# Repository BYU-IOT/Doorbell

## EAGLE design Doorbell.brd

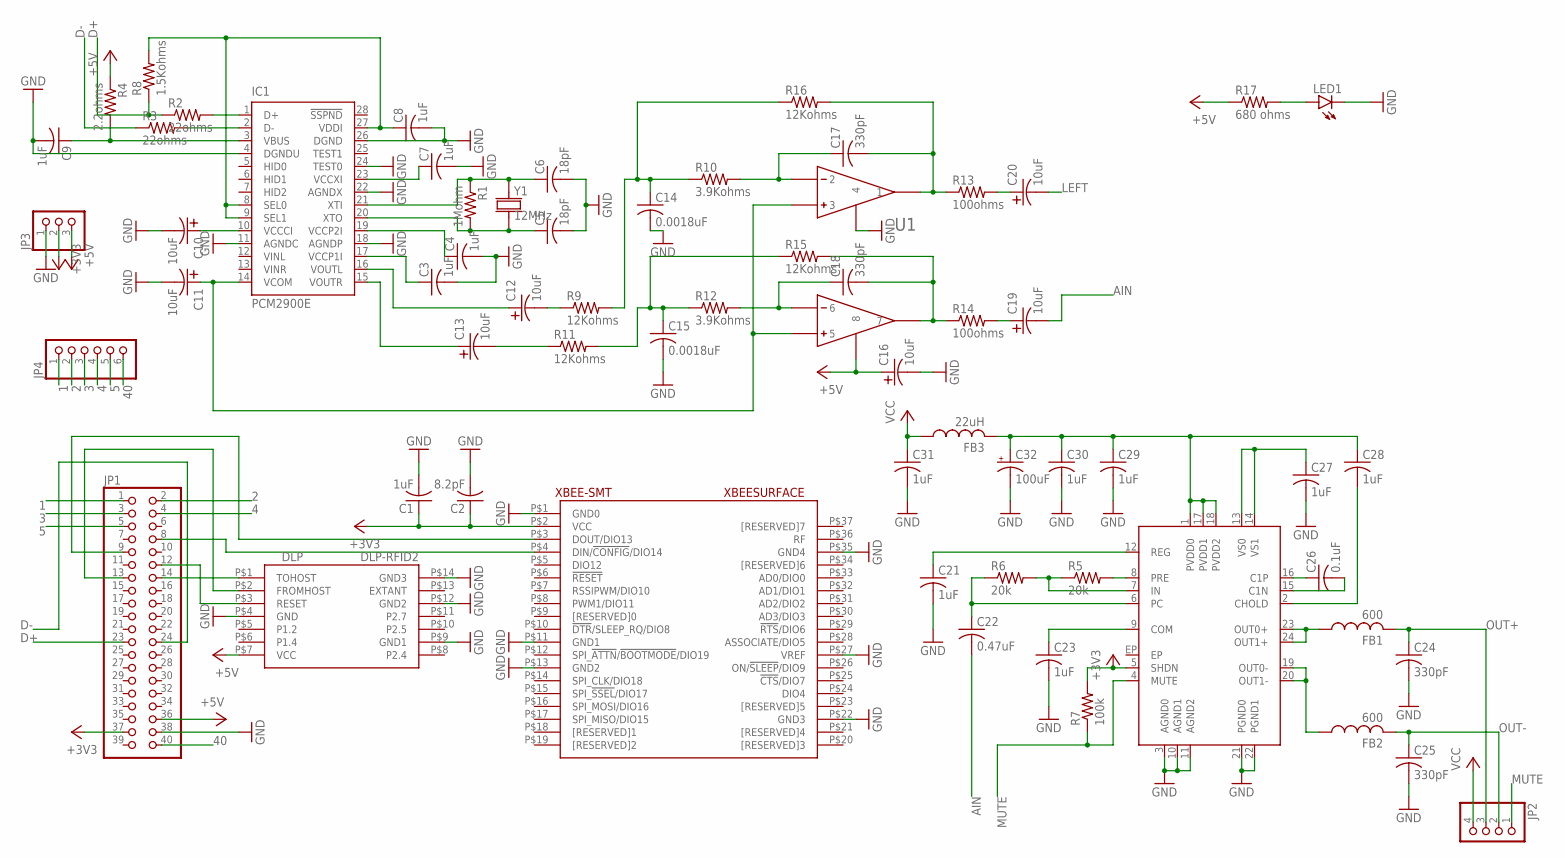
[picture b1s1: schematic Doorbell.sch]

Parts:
C1, C3, C4, C7, C8, C9, C21, C23, C27, C28, C29, C30, C31: 1uF; 0603_CAP
C2: 8.2pF; 0603_CAP
C5, C6: 18pF; 0603_CAP
C10, C11, C12, C13, C16, C19, C20: 10uF; 1411_CAP
C14, C15: 0.0018uF; 0603_CAP
C17, C18, C24, C25: 330pF; 0603_CAP
C22: 0.47uF; 0603_CAP
C26: 0.1uF; 0603_CAP
C32: 100uF; F_CAP
DLP: DLP-RFID2
FB1, FB2: 600; 0805_FB
FB3: 22uH; 0805_FB
IC1: PCM2900E; SSOP28DB
IC2: MAX9737; TQFN24
JP1: PINHD-2X20; 2X20
JP2: PINHD-1X4; 1X04
JP3: PINHD-1X3; 1X03
JP4: PINHD-1X6; 1X06
LED1: LED0603; 0603_LED
R1: 1Mohm; 0603_RESISTOR
R2, R3: 22ohms; 0603_RESISTOR
R4: 2.2ohms; 0603_RESISTOR
R5, R6: 20k; 0603_RESISTOR
R7: 100k; 0603_RESISTOR
R8: 1.5Kohms; 0603_RESISTOR
R9, R11, R15, R16: 12Kohms; 0603_RESISTOR
R10, R12: 3.9Kohms; 0603_RESISTOR
R13, R14: 100ohms; 0603_RESISTOR
R17: 680 ohms; 0603_RESISTOR
U1: OP-AMP; OPA2353UA
XBEE-SMT: XBEESURFACE
Y1: 12MHz; CRYSTAL_5X3

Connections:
1: JP1.1, JP4.1
2: JP1.2, JP4.2
3: JP1.3, JP4.3
4: JP1.4, JP4.4
5: JP1.5, JP4.5
40: JP1.40, JP4.6
+3V3: C1.1, C2.1, IC2.5 (SHDN), JP1.37, JP3.2, R7.2, XBEE-SMT.P$2 (VCC)
+5V: C16.P$1, DLP.P$7 (VCC), JP1.36, JP3.3, R4.1, R17.1, U1.P$8 (8)
AIN: C19.P$2, C22.2
D+: JP1.23, R2.1, R8.1
D-: JP1.24, R3.1
GND: C1.2, C2.2, C3.2, C4.2, C5.2, C6.2, C7.2, C8.2, C9.2, C10.P$2, C11.P$2, C14.2, C15.2, C16.P$2, C21.2, C23.2, C24.2, C25.2, C27.2, C29.2, C30.2, C31.2, C32.-, DLP.P$4 (GND), DLP.P$9 (GND1), DLP.P$12 (GND2), DLP.P$14 (GND3), IC1.4 (DGNDU), IC1.11 (AGNDC), IC1.18 (AGNDP), IC1.22 (AGNDX), IC1.24 (TEST0), IC1.26 (DGND), IC2.3 (AGND0), IC2.10 (AGND1), IC2.11 (AGND2), IC2.21 (PGND0), IC2.22 (PGND1), JP1.38, JP3.1, LED1.C, U1.P$4 (4), XBEE-SMT.P$1 (GND0), XBEE-SMT.P$11 (GND1), XBEE-SMT.P$13 (GND2), XBEE-SMT.P$22 (GND3), XBEE-SMT.P$27 (VREF), XBEE-SMT.P$35 (GND4)
LEFT: C20.P$2
MUTE: IC2.4 (MUTE), JP2.1, R7.1
unnamed: DLP.P$1 (TOHOST), JP1.14
unnamed: IC2.8 (PRE), R5.2
unnamed: IC2.7 (IN), R5.1, R6.2
unnamed: DLP.P$3 (RESET), JP1.12
unnamed: DLP.P$2 (FROMHOST), JP1.13
unnamed: JP1.8, XBEE-SMT.P$4 (DIN/!CONFIG!/DIO14)
unnamed: JP1.9, XBEE-SMT.P$3 (DOUT/DIO13)
unnamed: C3.1, IC1.17 (VCCP1I)
unnamed: IC1.1 (D+), R2.2
unnamed: C22.1, IC2.6 (PC), R6.1
unnamed: C8.1, IC1.8 (SEL0), IC1.9 (SEL1), IC1.27 (VDDI), R8.2
unnamed: IC1.2 (D-), R3.2
unnamed: C21.1, IC2.12 (REG)
unnamed: C7.1, IC1.23 (VCCXI)
unnamed: C6.1, IC1.21 (XTI), R1.1, Y1.1
unnamed: C5.1, IC1.20 (XTO), R1.2, Y1.2
unnamed: C4.1, IC1.19 (VCCP2I)
unnamed: C12.P$2, R9.1
unnamed: C13.P$2, R11.1
unnamed: C17.1, R10.2, U1.P$2 (2)
unnamed: C10.P$1, IC1.10 (VCCCI)
unnamed: C11.P$1, IC1.14 (VCOM), U1.P$3 (3), U1.P$5 (5)
unnamed: C18.1, R12.2, U1.P$6 (6)
unnamed: C12.P$1, IC1.16 (VOUTL)
unnamed: C13.P$1, IC1.15 (VOUTR)
unnamed: C14.1, R9.2, R10.1, R16.1
unnamed: C15.1, R11.2, R12.1, R15.1
unnamed: C17.2, R13.1, R16.2, U1.P$1 (1)
unnamed: C18.2, R14.1, R15.2, U1.P$7 (7)
unnamed: LED1.A, R17.2
unnamed: C20.P$1, R13.2
unnamed: C19.P$1, R14.2
unnamed: C9.1, IC1.3 (VBUS), R4.2
unnamed: C23.1, IC2.9 (COM)
unnamed: FB1.1, IC2.23 (OUT0+), IC2.24 (OUT1+)
unnamed: FB2.1, IC2.19 (OUT0-), IC2.20 (OUT1-)
unnamed: C26.1, IC2.16 (C1P)
unnamed: C26.2, IC2.15 (C1N)
unnamed: C28.2, IC2.2 (CHOLD)
unnamed: C28.1, C29.1, C30.1, C32.+, FB3.2, IC2.1 (PVDD0), IC2.17 (PVDD1), IC2.18 (PVDD2)
unnamed: C27.1, IC2.13 (VS0), IC2.14 (VS1)
OUT+: C24.1, FB1.2, JP2.3
OUT-: C25.1, FB2.2, JP2.2
VCC: C31.1, FB3.1, JP2.4

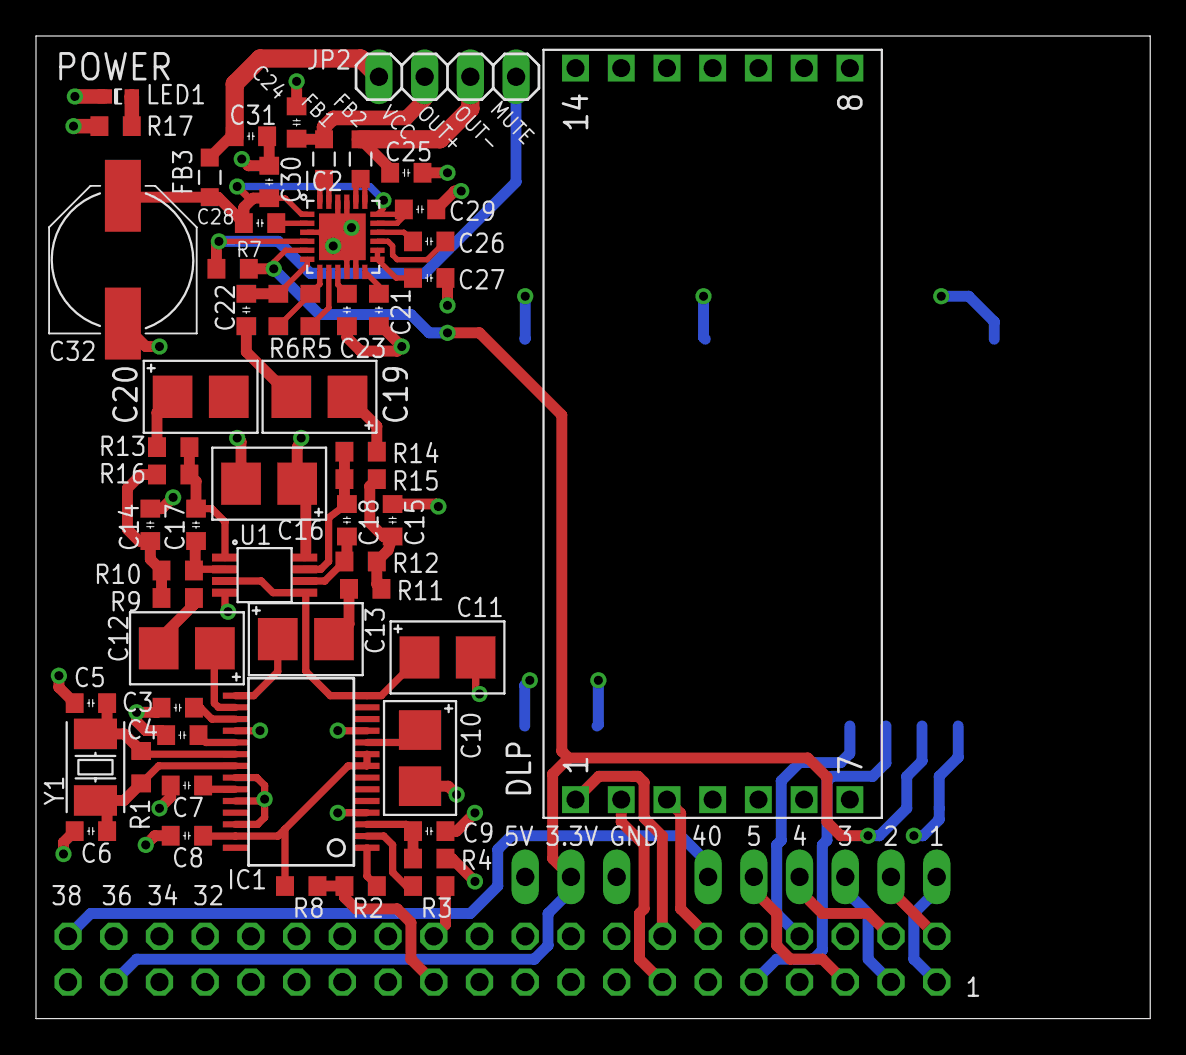
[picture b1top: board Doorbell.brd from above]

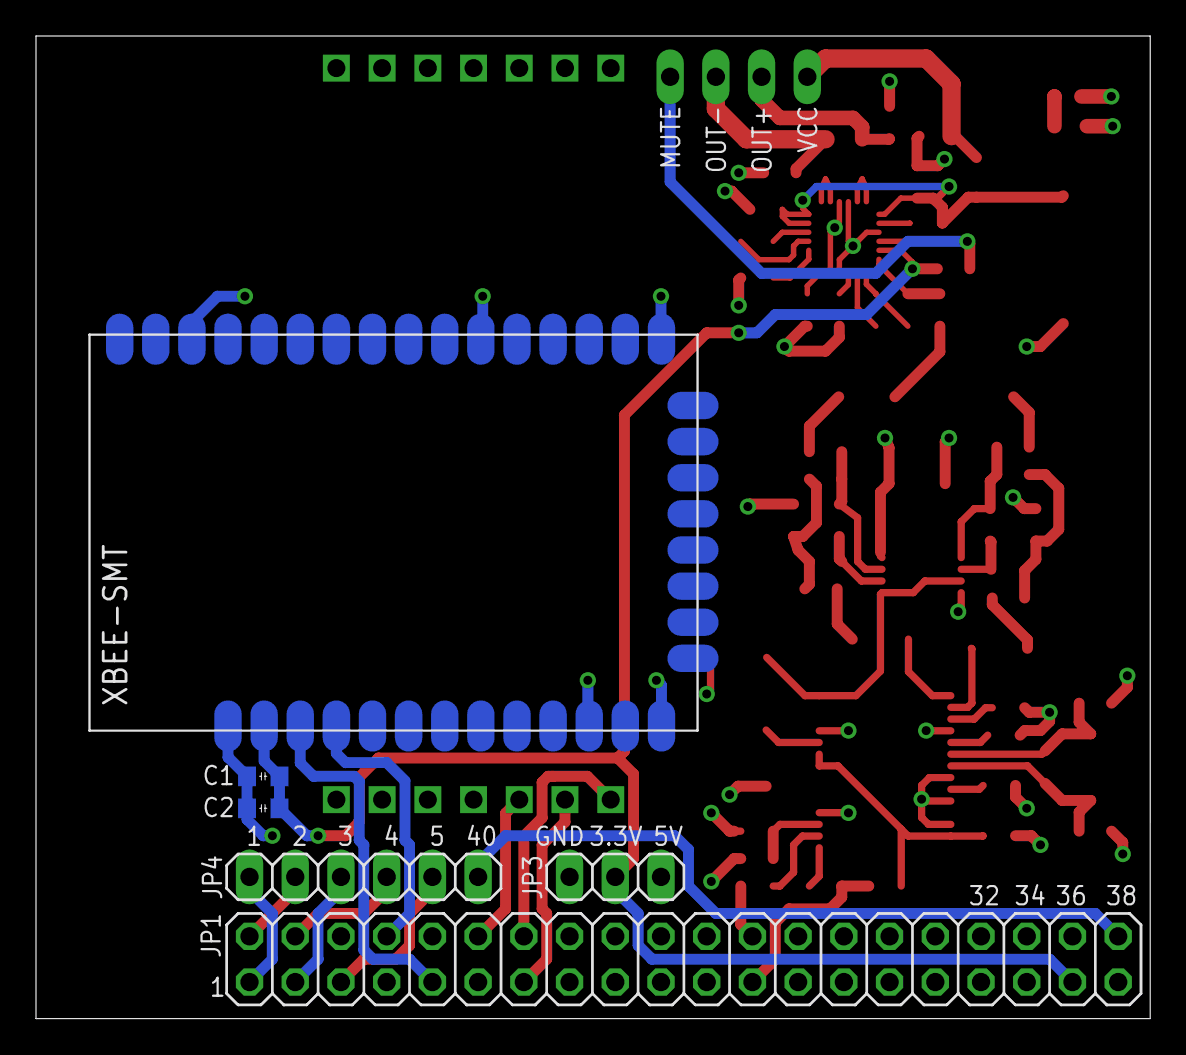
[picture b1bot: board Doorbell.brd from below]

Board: 4 copper layers, 61.9 x 54.6 mm, 63 parts (6 on the bottom side), 57 nets.

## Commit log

2017-05-13 PCB files of Doorbell Coordinator
    This has all the files for the doorbell PCB and it’s gerber files and a
    bill of materials and a pdf of the board.
